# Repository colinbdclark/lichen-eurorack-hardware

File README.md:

# Lichen Community Systems Eurorack Hardware Designs

A collection hardware schematics and PCB designs for Lichen Community Systems' experimental Eurorack modules. They were created with KiCad.

## License

These designs are Copyright 2023-5, Colin Clark. They are shared under the [Creative Commons Attribution Non-Commercial Share Alike 4.0](https://creativecommons.org/licenses/by-nc-sa/4.0/) license.

### Symbols and Footprints Library

The Lichen Kicad [symbols and footprints libraries](Lichen.pretty) were largely derived from KiCAD library symbols, and are made available under the same license:
https://kicad.org/libraries/license/

licensed under the Creative Commons CC-BY-SA 4.0 License
(https://creativecommons.org/licenses/by-sa/4.0/legalcode), with the following
exception:

To the extent that the creation of electronic designs that use
'Licensed Material' can be considered to be 'Adapted Material', then the
copyright holder waives article 3 of the license with respect to these designs
and any generated files which use data provided as part of the
'Licensed Material'.

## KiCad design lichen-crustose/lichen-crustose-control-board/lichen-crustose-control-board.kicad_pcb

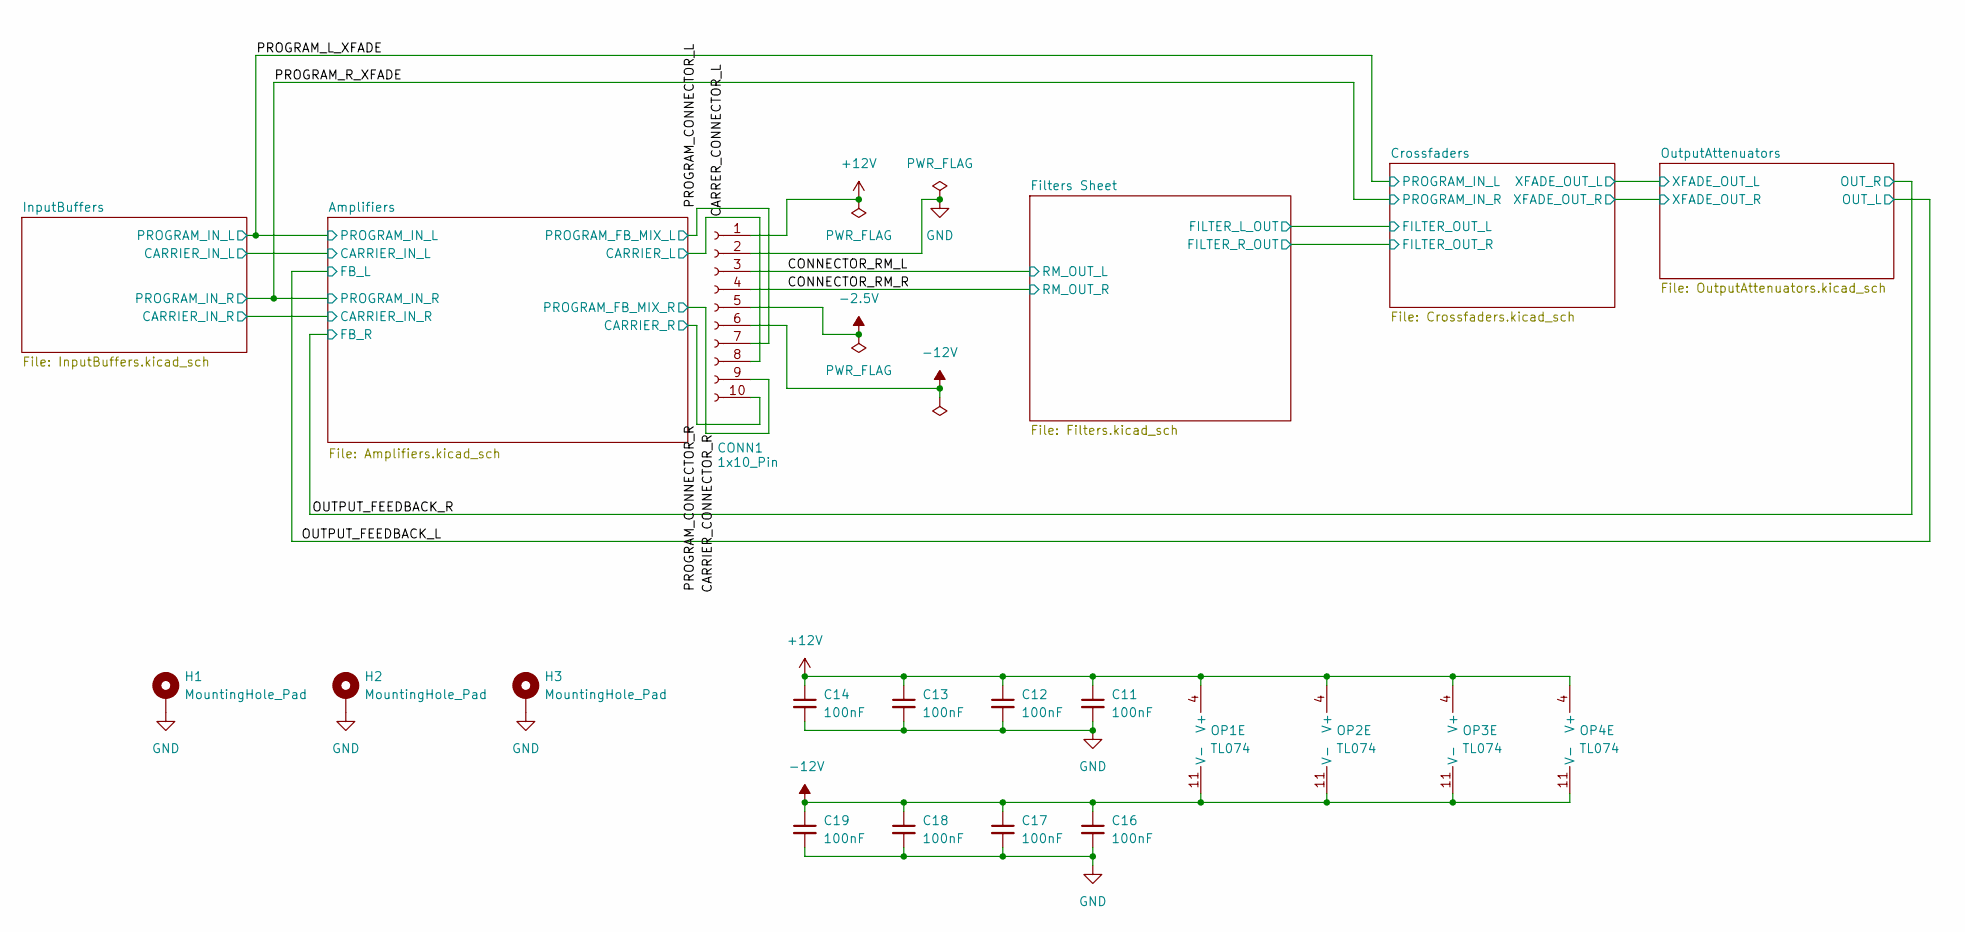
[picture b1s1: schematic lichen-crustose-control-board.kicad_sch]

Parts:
C11, C12, C13, C14, C16, C17, C18, C19: 100nF; C_0402_1005Metric_small_pads; Part Number CL05B104KB54PNC; LCSC C307331
CONN1: 1x10_Pin; PinHeader_1x10_P2.54mm_Vertical
H1, H2, H3: MountingHole_Pad; MountingHole_2.2mm_M2_Pad
OP1, OP2, OP3, OP4: TL074; SOIC-14_3.9x8.7mm_P1.27mm; Part Number TL074IDR; LCSC C6964

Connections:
+12V: C11.1, C12.1, C13.1, C14.1, CONN1.1, OP1.4 (V+), OP2.4 (V+), OP3.4 (V+), OP4.4 (V+)
-2.5V: CONN1.5; also elsewhere on the board
-12V: C16.1, C17.1, C18.1, C19.1, CONN1.6, OP1.11 (V-), OP2.11 (V-), OP3.11 (V-), OP4.11 (V-)
/CARRER_CONNECTOR_L: CONN1.8; also elsewhere on the board
/CARRIER_CONNECTOR_R: CONN1.9; also elsewhere on the board
/CONNECTOR_RM_L: CONN1.3; also elsewhere on the board
/CONNECTOR_RM_R: CONN1.4; also elsewhere on the board
/PROGRAM_CONNECTOR_L: CONN1.7; also elsewhere on the board
/PROGRAM_CONNECTOR_R: CONN1.10; also elsewhere on the board
GND: C11.2, C12.2, C13.2, C14.2, C16.2, C17.2, C18.2, C19.2, CONN1.2, H1.1, H2.1, H3.1; also elsewhere on the board

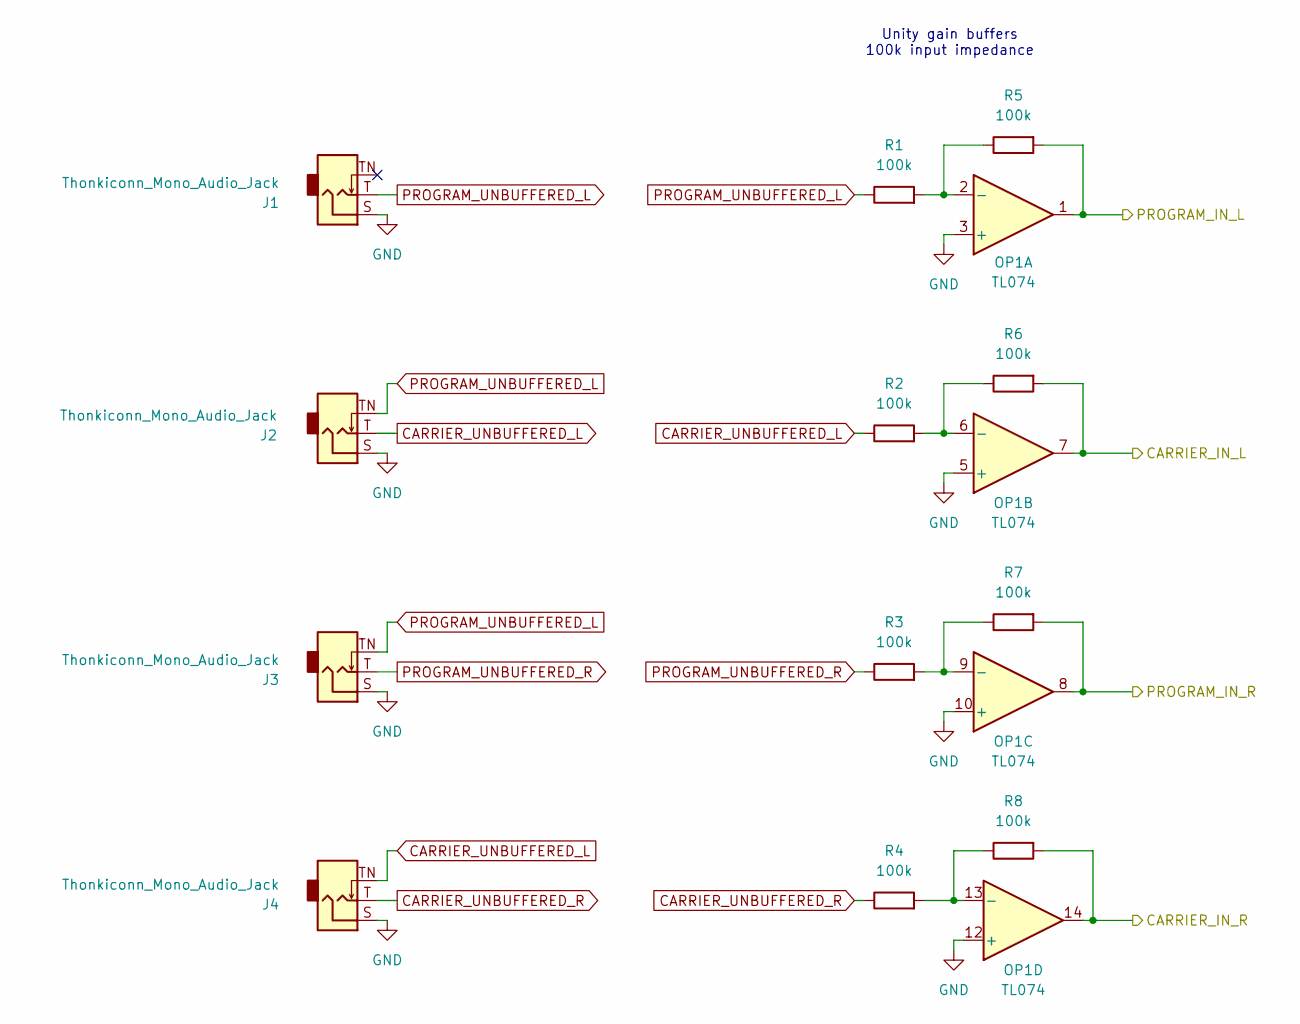
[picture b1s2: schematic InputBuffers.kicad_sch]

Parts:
J1, J2, J3, J4: Thonkiconn_Mono_Audio_Jack; Audio_Jack_Thonkiconn_Mono; Part Number WQP518MA/PJ398SM
OP1: TL074; SOIC-14_3.9x8.7mm_P1.27mm; Part Number TL074IDR; LCSC C6964
R1, R2, R3, R4, R5, R6, R7: 100K; R_0603; Part Number 0603WAF1003T5E; LCSC C25803
R8: 100K; R_0603; Part Number 0603WAF1003T5E; JLCPCB ID C25803

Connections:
/Amplifiers/CARRIER_IN_L: OP1.7, R6.2; also elsewhere on the board
/Amplifiers/CARRIER_IN_R: OP1.14, R8.2; also elsewhere on the board
/PROGRAM_L_XFADE: OP1.1, R5.2; also elsewhere on the board
/PROGRAM_R_XFADE: OP1.8, R7.2; also elsewhere on the board
CARRIER_UNBUFFERED_L: J2.T, J4.TN, R2.1
CARRIER_UNBUFFERED_R: J4.T, R4.1
GND: J1.S, J2.S, J3.S, J4.S, OP1.3 (+), OP1.5 (+), OP1.10 (+), OP1.12 (+); also elsewhere on the board
unnamed: OP1.2 (-), R1.2, R5.1
unnamed: OP1.6 (-), R2.2, R6.1
unnamed: OP1.9 (-), R3.2, R7.1
unnamed: OP1.13 (-), R4.2, R8.1
PROGRAM_UNBUFFERED_L: J1.T, J2.TN, J3.TN, R1.1
PROGRAM_UNBUFFERED_R: J3.T, R3.1

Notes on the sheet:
Unity gain buffers 100k input impedance

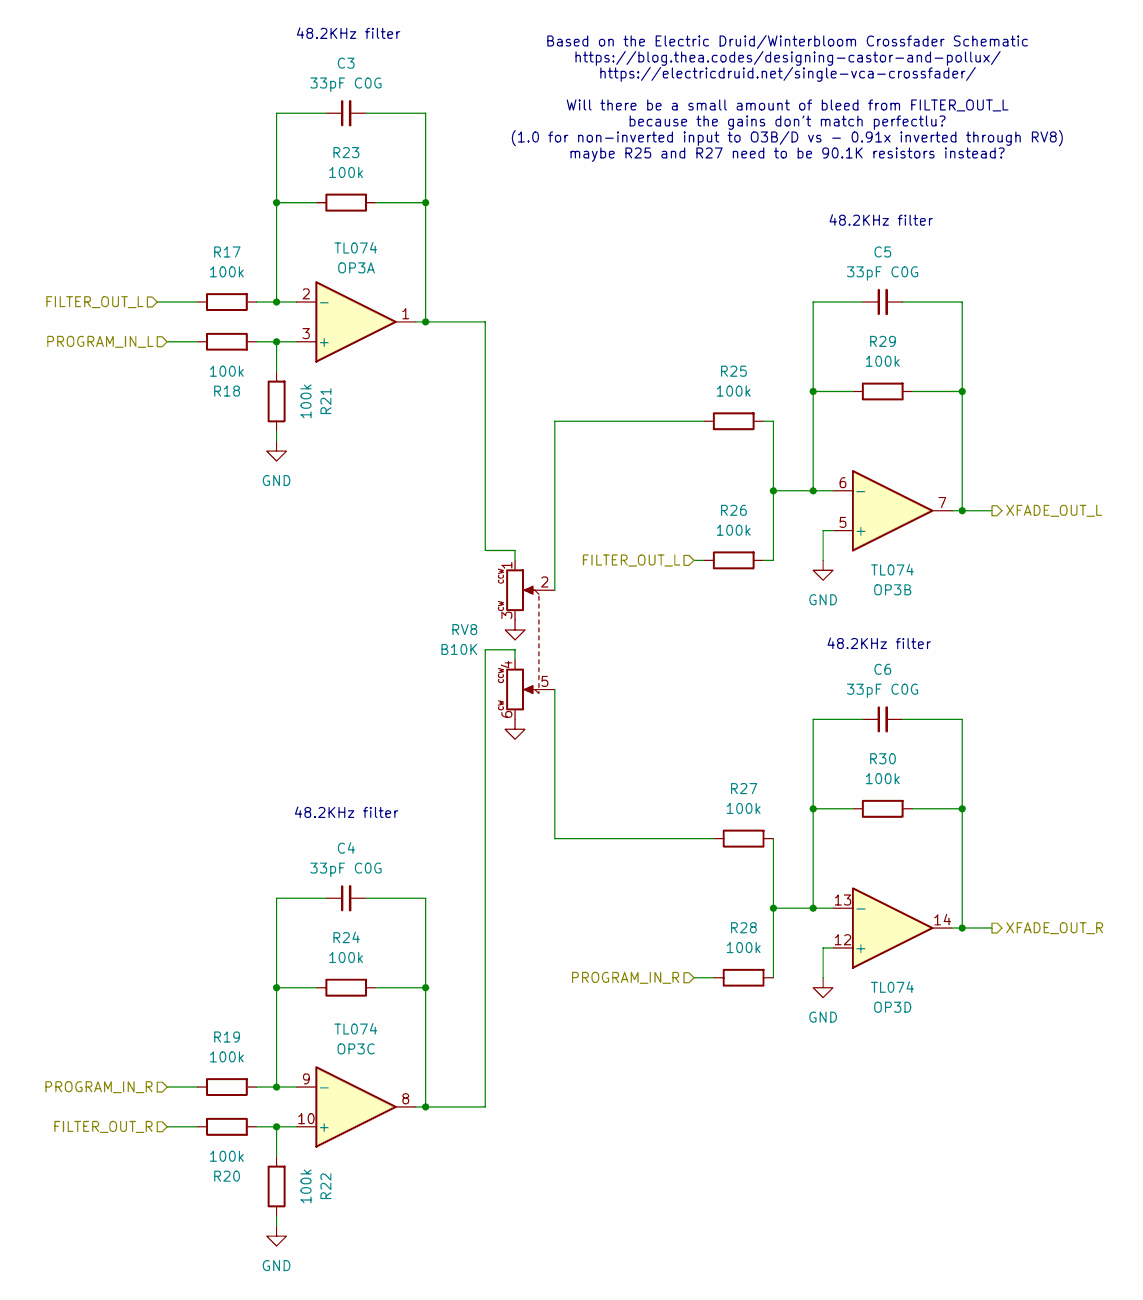
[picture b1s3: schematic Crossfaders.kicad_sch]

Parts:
C3, C4, C5, C6: 33pF C0G; C_0603; Part Number CL10C330JB8NNNC; LCSC C1663
OP3: TL074; SOIC-14_3.9x8.7mm_P1.27mm; Part Number TL074IDR; LCSC C6964
R17, R18, R19, R20, R21, R22, R23, R24, R25, R26, R27, R28, R29, R30: 100K; R_0603; Part Number 0603WAF1003T5E; LCSC C25803
RV8: B10K; Potentiometer_Alpha_RD902F-40-00D_Dual_Vertical; Part Number RD90F-40

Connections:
/Crossfaders/FILTER_OUT_L: R17.1, R26.1; also elsewhere on the board
/Crossfaders/FILTER_OUT_R: R20.1; also elsewhere on the board
/Crossfaders/XFADE_OUT_L: C5.2, OP3.7, R29.2; also elsewhere on the board
/Crossfaders/XFADE_OUT_R: C6.2, OP3.14, R30.2; also elsewhere on the board
/PROGRAM_L_XFADE: R18.1; also elsewhere on the board
/PROGRAM_R_XFADE: R19.1, R28.1; also elsewhere on the board
GND: OP3.5 (+), OP3.12 (+), R21.1, R22.1, RV8.3, RV8.6; also elsewhere on the board
unnamed: C3.2, OP3.1, R23.2, RV8.1
unnamed: C4.2, OP3.8, R24.2, RV8.4
unnamed: OP3.3 (+), R18.2, R21.2
unnamed: C3.1, OP3.2 (-), R17.2, R23.1
unnamed: C5.1, OP3.6 (-), R25.2, R26.2, R29.1
unnamed: OP3.10 (+), R20.2, R22.2
unnamed: C4.1, OP3.9 (-), R19.2, R24.1
unnamed: C6.1, OP3.13 (-), R27.2, R28.2, R30.1
unnamed: R25.1, RV8.2
unnamed: R27.1, RV8.5

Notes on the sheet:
Based on the Electric Druid/Winterbloom Crossfader Schematic https://blog.thea.codes/designing-castor-and-pollux/ https://electricdruid.net/single-vca-crossfader/ Will there be a small amount of bleed from FILTER_OUT_L because the gains don't match perfectlu? (1.0 for non-inverted input to O3B/D vs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
48.2KHz filter

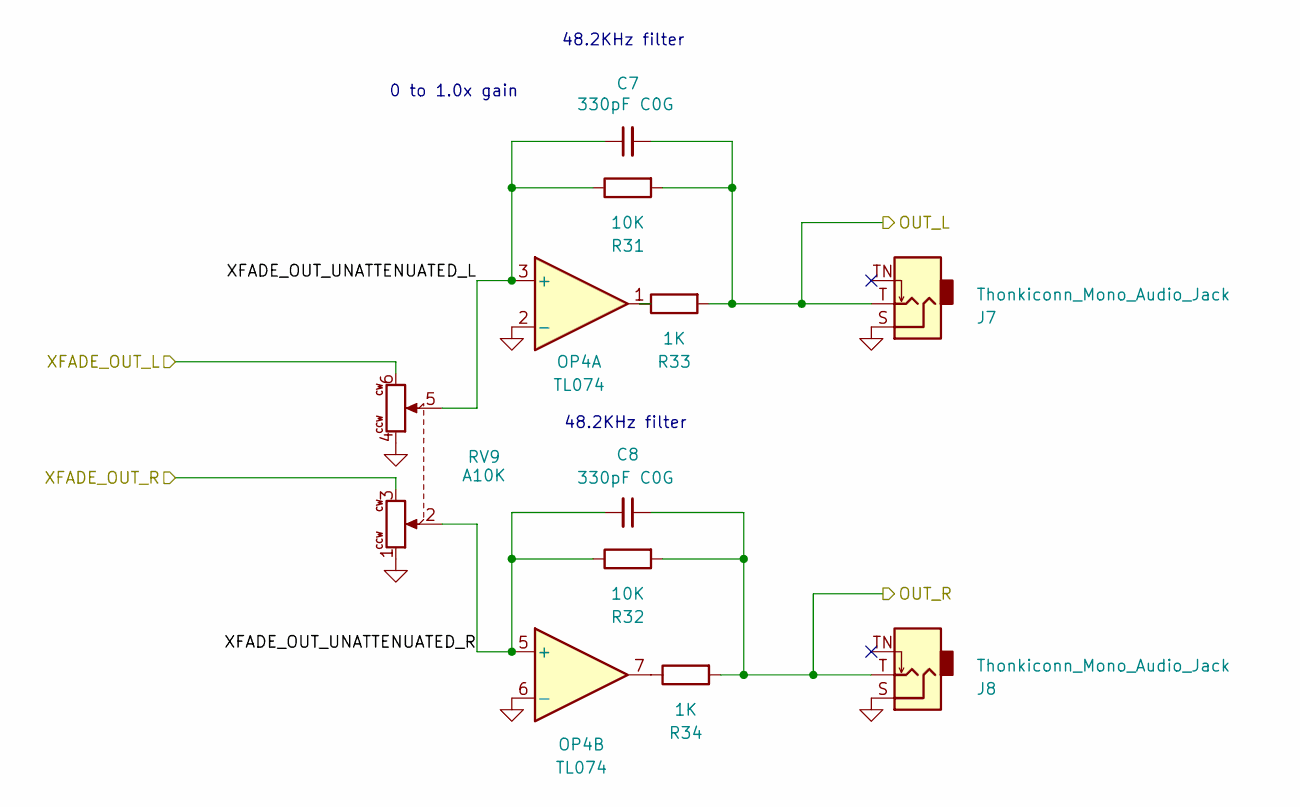
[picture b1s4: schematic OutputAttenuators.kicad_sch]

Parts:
C7, C8: 330pF C0G; C_0603; Part Number CL10C331JB8NNNC; LCSC C1664
J7, J8: Thonkiconn_Mono_Audio_Jack; Audio_Jack_Thonkiconn_Mono; Part Number WQP518MA/PJ398SM
OP4: TL074; SOIC-14_3.9x8.7mm_P1.27mm; Part Number TL074IDR; LCSC C6964
R31, R32: 10K; R_0603; Part Number 0603WAF1002T5E; LCSC C25804
R33, R34: 1K; R_0603; Part Number 0603WAF1001T5E; LCSC C21190
RV9: A10K; Potentiometer_Alpha_RD902F-40-00D_Dual_Vertical; Part Number RD90F-40

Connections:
/Crossfaders/XFADE_OUT_L: RV9.6; also elsewhere on the board
/Crossfaders/XFADE_OUT_R: RV9.3; also elsewhere on the board
/OUTPUT_FEEDBACK_L: C7.2, J7.T, R31.2, R33.2; also elsewhere on the board
/OUTPUT_FEEDBACK_R: C8.1, J8.T, R32.2, R34.2; also elsewhere on the board
/OutputAttenuators/XFADE_OUT_UNATTENUATED_L: C7.1, OP4.3 (+), R31.1, RV9.5
/OutputAttenuators/XFADE_OUT_UNATTENUATED_R: C8.2, OP4.5 (+), R32.1, RV9.2
GND: J7.S, J8.S, OP4.2 (-), OP4.6 (-), RV9.1, RV9.4; also elsewhere on the board
unnamed: OP4.1, R33.1
unnamed: OP4.7, R34.1

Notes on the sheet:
48.2KHz filter
0 to 1.0x gain

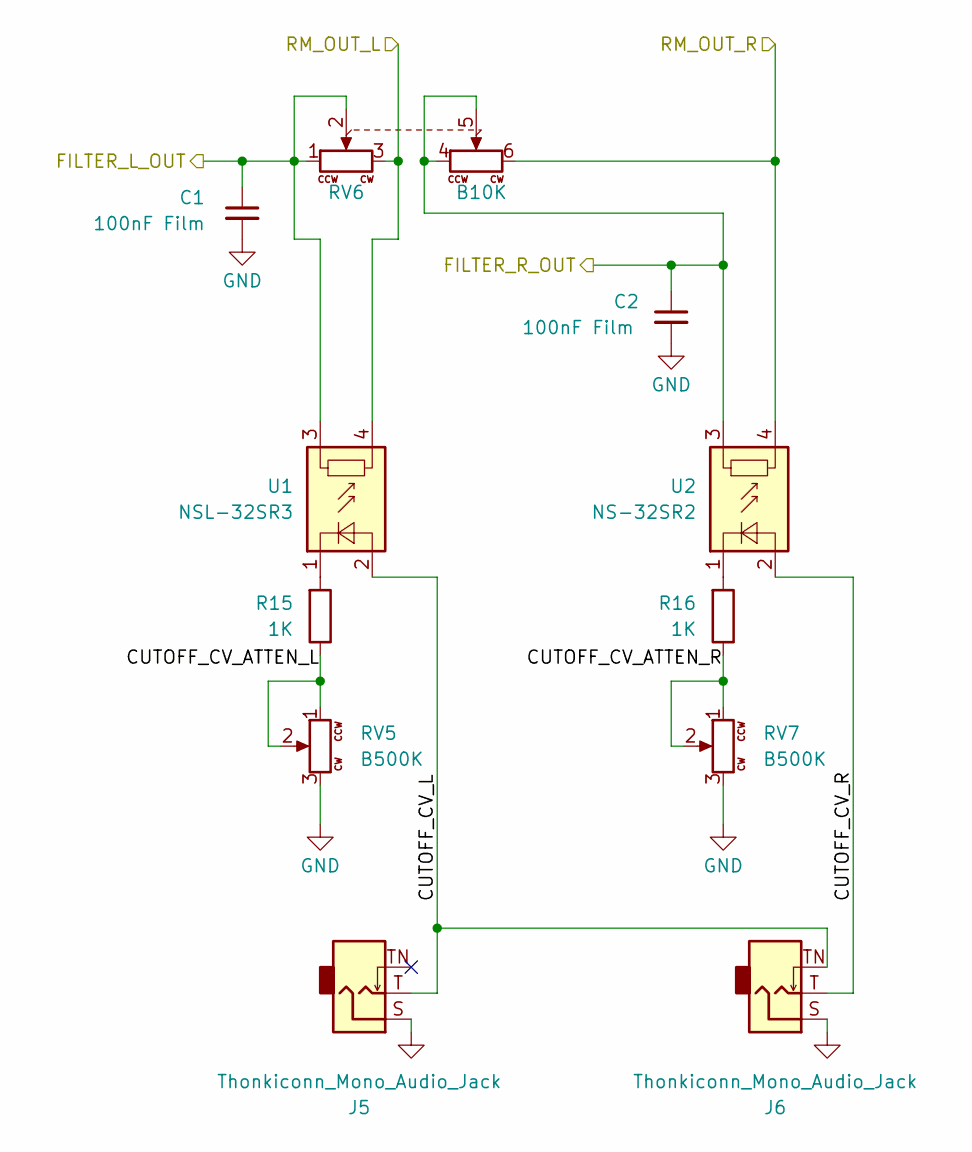
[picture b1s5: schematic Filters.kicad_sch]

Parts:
C1, C2: 100nF Film; C_1210; Part Number ECHU1C104GX5; LCSC C569766
J5, J6: Thonkiconn_Mono_Audio_Jack; Audio_Jack_Thonkiconn_Mono; Part Number WQP518MA/PJ398SM
R15, R16: 1K; R_0603; Part Number 0603WAF1001T5E; LCSC C21190
RV5, RV7: B500K; Potentiometer_Alpha_RD901_Eurorack; Part Number RD901F-40
RV6: B10K; Potentiometer_Alpha_RD902F-40-00D_Dual_Vertical; Part Number RD90F-40
U1: NSL-32SR3; NSL-32
U2: NS-32SR2; NSL-32

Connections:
/CONNECTOR_RM_L: RV6.3, U1.4; also elsewhere on the board
/CONNECTOR_RM_R: RV6.6, U2.4; also elsewhere on the board
/Crossfaders/FILTER_OUT_L: C1.1, RV6.1, RV6.2, U1.3; also elsewhere on the board
/Crossfaders/FILTER_OUT_R: C2.1, RV6.4, RV6.5, U2.3; also elsewhere on the board
/Filters Sheet/CUTOFF_CV_ATTEN_L: R15.1, RV5.1, RV5.2
/Filters Sheet/CUTOFF_CV_ATTEN_R: R16.1, RV7.1, RV7.2
/Filters Sheet/CUTOFF_CV_L: J5.T, J6.TN, U1.2 (+)
/Filters Sheet/CUTOFF_CV_R: J6.T, U2.2 (+)
GND: C1.2, C2.2, J5.S, J6.S, RV5.3, RV7.3; also elsewhere on the board
unnamed: R15.2, U1.1 (-)
unnamed: R16.2, U2.1 (-)

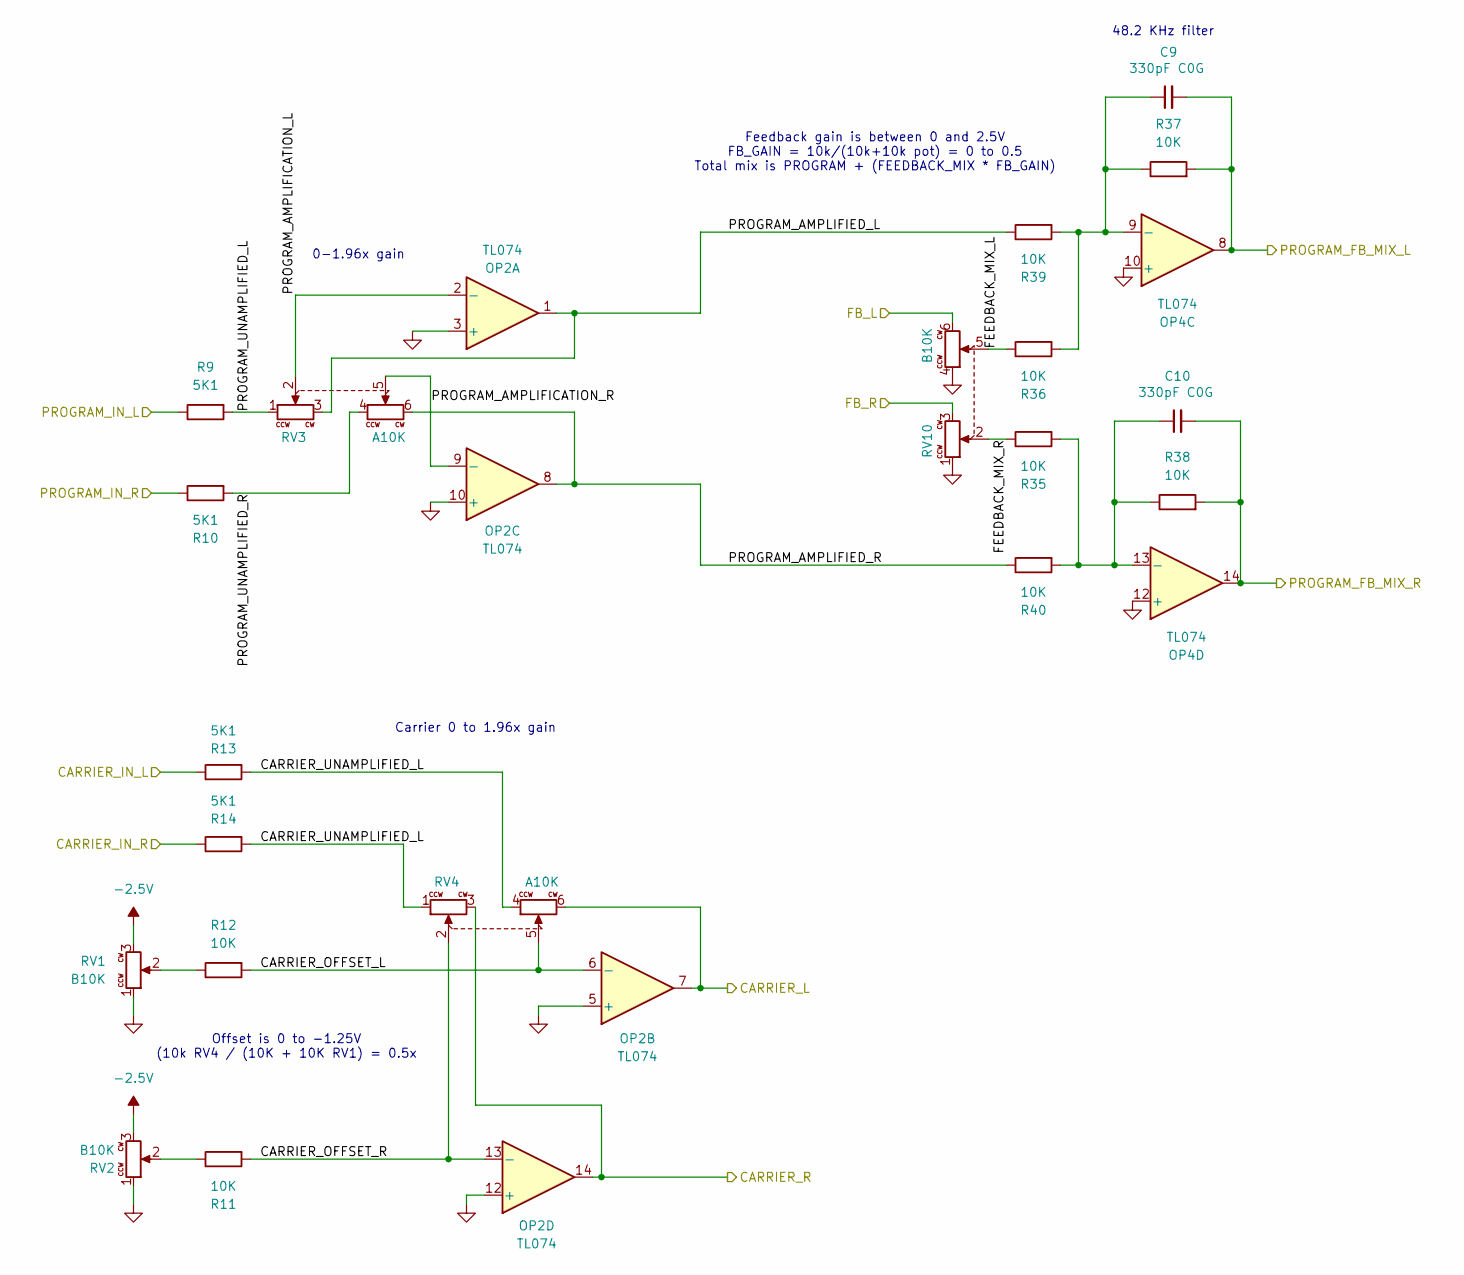
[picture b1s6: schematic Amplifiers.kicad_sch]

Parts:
C9, C10: 330pF C0G; C_0603; Part Number CL10C331JB8NNNC; LCSC C1664
OP2, OP4: TL074; SOIC-14_3.9x8.7mm_P1.27mm; Part Number TL074IDR; LCSC C6964
R9, R10, R13, R14: 5.1K; R_0603; Part Number 0603WAF5101T5E; LCSC C23186
R11, R12, R35, R36, R37, R38, R39, R40: 10K; R_0603; Part Number 0603WAF1002T5E; LCSC C25804
RV1, RV2: B10K; Potentiometer_Alpha_RD901_Eurorack; Part Number RD901F-40
RV3, RV4: A10K; Potentiometer_Alpha_RD902F-40-00D_Dual_Vertical; Part Number RD90F-40
RV10: B10K; Potentiometer_Alpha_RD902F-40-00D_Dual_Vertical; Part Number RD90F-40

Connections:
-2.5V: RV1.3, RV2.3; also elsewhere on the board
/Amplifiers/CARRIER_IN_L: R13.1; also elsewhere on the board
/Amplifiers/CARRIER_IN_R: R14.1; also elsewhere on the board
/Amplifiers/CARRIER_OFFSET_L: OP2.6 (-), R12.2, RV4.5
/Amplifiers/CARRIER_OFFSET_R: OP2.13 (-), R11.2, RV4.2
/Amplifiers/CARRIER_UNAMPLIFIED_L: R13.2, R14.2, RV4.1, RV4.4
/Amplifiers/FEEDBACK_MIX_L: R36.1, RV10.5
/Amplifiers/FEEDBACK_MIX_R: R35.1, RV10.2
/Amplifiers/PROGRAM_AMPLIFICATION_L: OP2.2 (-), RV3.2
/Amplifiers/PROGRAM_AMPLIFICATION_R: OP2.9 (-), RV3.5
/Amplifiers/PROGRAM_AMPLIFIED_L: OP2.1, R39.1, RV3.3
/Amplifiers/PROGRAM_AMPLIFIED_R: OP2.8, R40.1, RV3.6
/Amplifiers/PROGRAM_UNAMPLIFIED_L: R9.2, RV3.1
/Amplifiers/PROGRAM_UNAMPLIFIED_R: R10.2, RV3.4
/CARRER_CONNECTOR_L: OP2.7, RV4.6; also elsewhere on the board
/CARRIER_CONNECTOR_R: C10.2, OP4.14, R38.2; also elsewhere on the board
/OUTPUT_FEEDBACK_L: RV10.6; also elsewhere on the board
/OUTPUT_FEEDBACK_R: RV10.3; also elsewhere on the board
/PROGRAM_CONNECTOR_L: C9.2, OP4.8, R37.2; also elsewhere on the board
/PROGRAM_CONNECTOR_R: OP2.14, RV4.3; also elsewhere on the board
/PROGRAM_L_XFADE: R9.1; also elsewhere on the board
/PROGRAM_R_XFADE: R10.1; also elsewhere on the board
GND: OP2.3 (+), OP2.5 (+), OP2.10 (+), OP2.12 (+), OP4.10 (+), OP4.12 (+), RV1.1, RV2.1, RV10.1, RV10.4; also elsewhere on the board
unnamed: C9.1, OP4.9 (-), R36.2, R37.1, R39.2
unnamed: C10.1, OP4.13 (-), R35.2, R38.1, R40.2
unnamed: R11.1, RV2.2
unnamed: R12.1, RV1.2

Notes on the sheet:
Offset is 0 to -1.25V (10k RV4 / (10K + 10K RV1) = 0.5x
Feedback gain is between 0 and 2.5V FB_GAIN = 10k/(10k+10k pot) = 0 to 0.5 Total mix is PROGRAM + (FEEDBACK_MIX * FB_GAIN)
48.2 KHz filter
0-1.96x gain
Carrier 0 to 1.96x gain

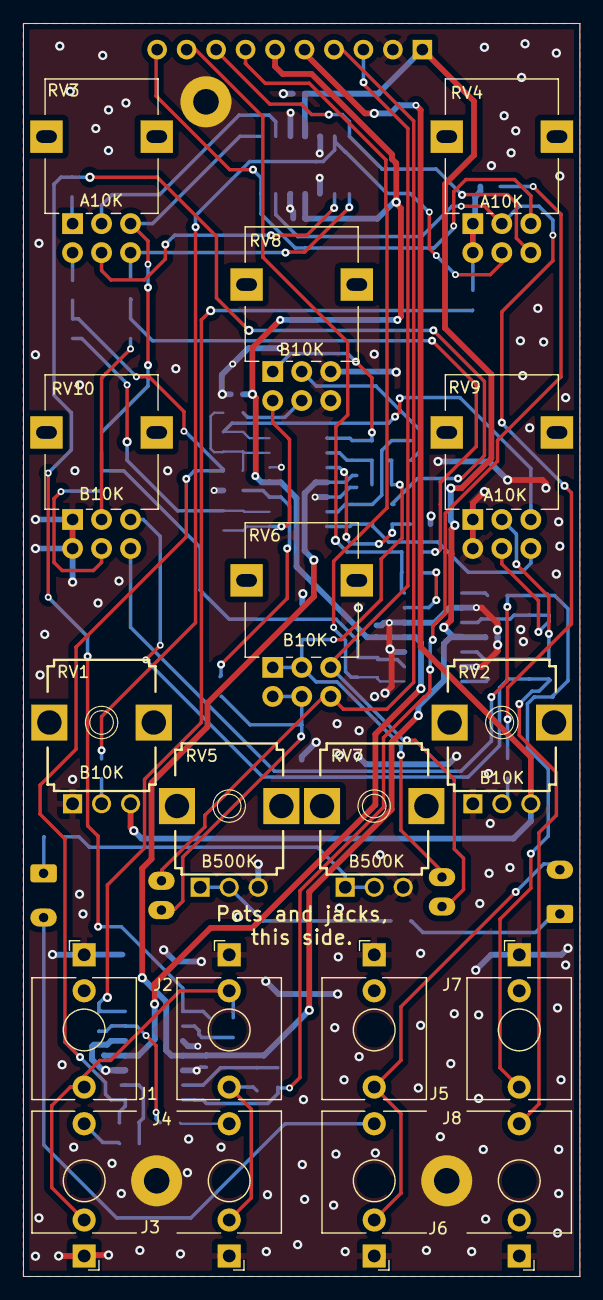
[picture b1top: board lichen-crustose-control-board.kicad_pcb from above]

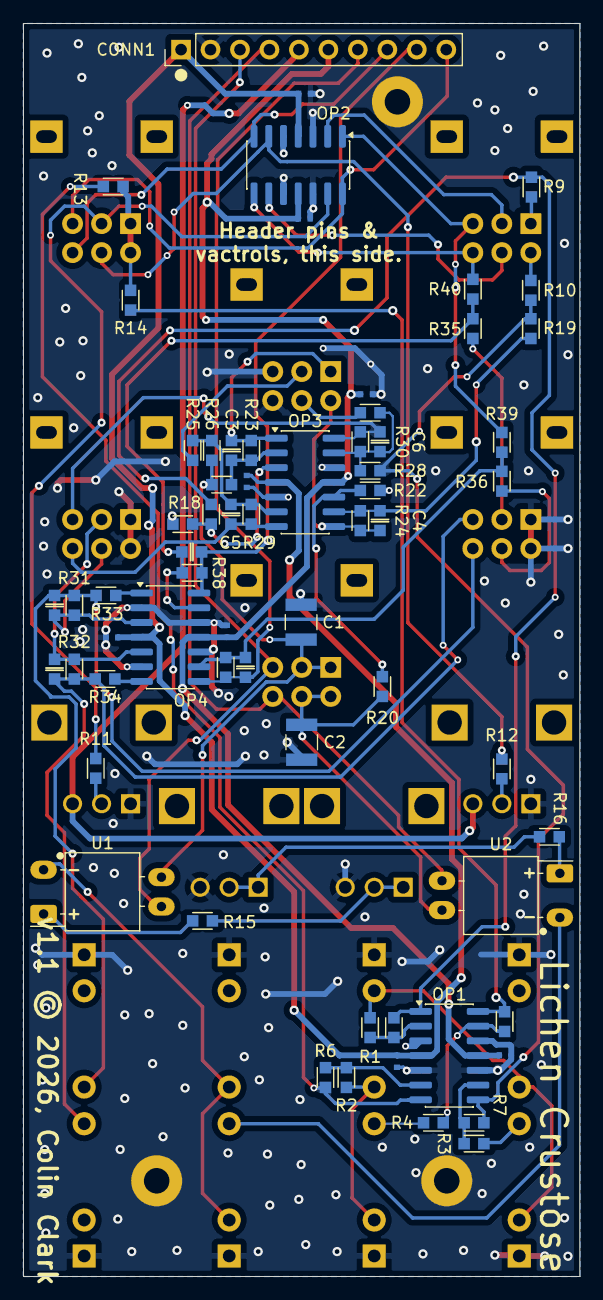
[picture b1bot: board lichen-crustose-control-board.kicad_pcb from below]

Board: 2 copper layers, 48.0 x 108.0 mm, 86 parts (67 on the bottom side), 63 nets.

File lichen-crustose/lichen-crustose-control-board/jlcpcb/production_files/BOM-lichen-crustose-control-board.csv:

Comment,Designator,Footprint,LCSC,Quantity
33pF C0G,"C3,C4,C5,C6",C_0603,C1663,4
330pF C0G,"C10,C7,C8,C9",C_0603,C1664,4
1K,"R15,R16,R33,R34",R_0603,C21190,4
5.1K,"R10,R13,R14,R9",R_0603,C23186,4
100K,"R1,R17,R18,R19,R2,R20,R21,R22,R23,R24,R25,R26,R27,R28,R29,R3,R30,R5,R6,R7,R8",R_0603,C25803,21
10K,"R11,R12,R31,R32,R35,R36,R37,R38,R39,R4,R40",R_0603,C25804,11
100nF,"C11,C12,C13,C14,C16,C17,C18,C19",C_0402_1005Metric_small_pads,C307331,8
100nF Film,"C1,C2",C_1210,C569766,2
TL074,"OP1,OP2,OP3,OP4",SOIC-14_3.9x8.7mm_P1.27mm,C6964,4

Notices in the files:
active-vactrol-vca/active-vactrol-vca-board/active-vactrol-vca-board.kicad_pcb:
Copyright 2026, Lichen Community Systems
lichen-crustose/lichen-crustose-control-board/lichen-crustose-control-board.kicad_pcb:
v1.1 © 2026, Colin Clark
lichen-stereo-klein-filter/lichen-stereo-klein-filter-board/lichen-stereo-klein-filter-board.kicad_pcb:
v1.0 © 2026, Colin Clark
